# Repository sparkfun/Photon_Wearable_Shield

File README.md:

SparkFun Photon Wearable Shield

========================================

[*SparkFun Photon Wearable Shield (DEV-13328)*](https://www.sparkfun.com/products/13328)

The SparkFun Photon Wearable Shield makes it easy to add the WiFi enabled Photon to any wearables project. Each pin on the Photon is broken out into large sewing pins. Use conductive thread to make your next wearables projects. The large pins are also great for using conductive paint to create any project that needs WiFi. There are even optional smaller pins for soldering flexible wires. The SparkFun Photon Wearable Shield comes with the headers already soldered on, so you can plug and play!

The Particle Photon is a tiny WiFi development kit for creating connected projects and products. Sporting a 120Mhz ARM Cortex M3 and built-in WiFi, the Photon is not only powerful, but easy to use. The small form factor is ideal for IoT projects with cloud-connectivity.

Note: This Photon Wearable Shield does not include a Photon module and is currently available for preorder with a tentative release date of June 2015.

Features:

* 24 Large Sewing Tabs
* Headers and Connectors Pre-Soldered
* Compatible with the Photon and the Core

Repository Contents
-------------------

* **/Production** - Production panel files (.brd)
* **/Hardware** - Eagle design files (.brd, .sch)

Documentation
--------------
* **[SparkFun Photon Wearable Shield Hookup Guide](https://learn.sparkfun.com/tutorials/photon-wearable-shield-hookup-guide-)** - Basic hookup guide for the SparkFun Photon Wearable Shield.

License Information
-------------------

This product is _**open source**_! 

Please review the LICENSE.md file for license information. 

If you have any questions or concerns on licensing, please contact techsupport@sparkfun.com.

Distributed as-is; no warranty is given.

- Your friends at SparkFun.

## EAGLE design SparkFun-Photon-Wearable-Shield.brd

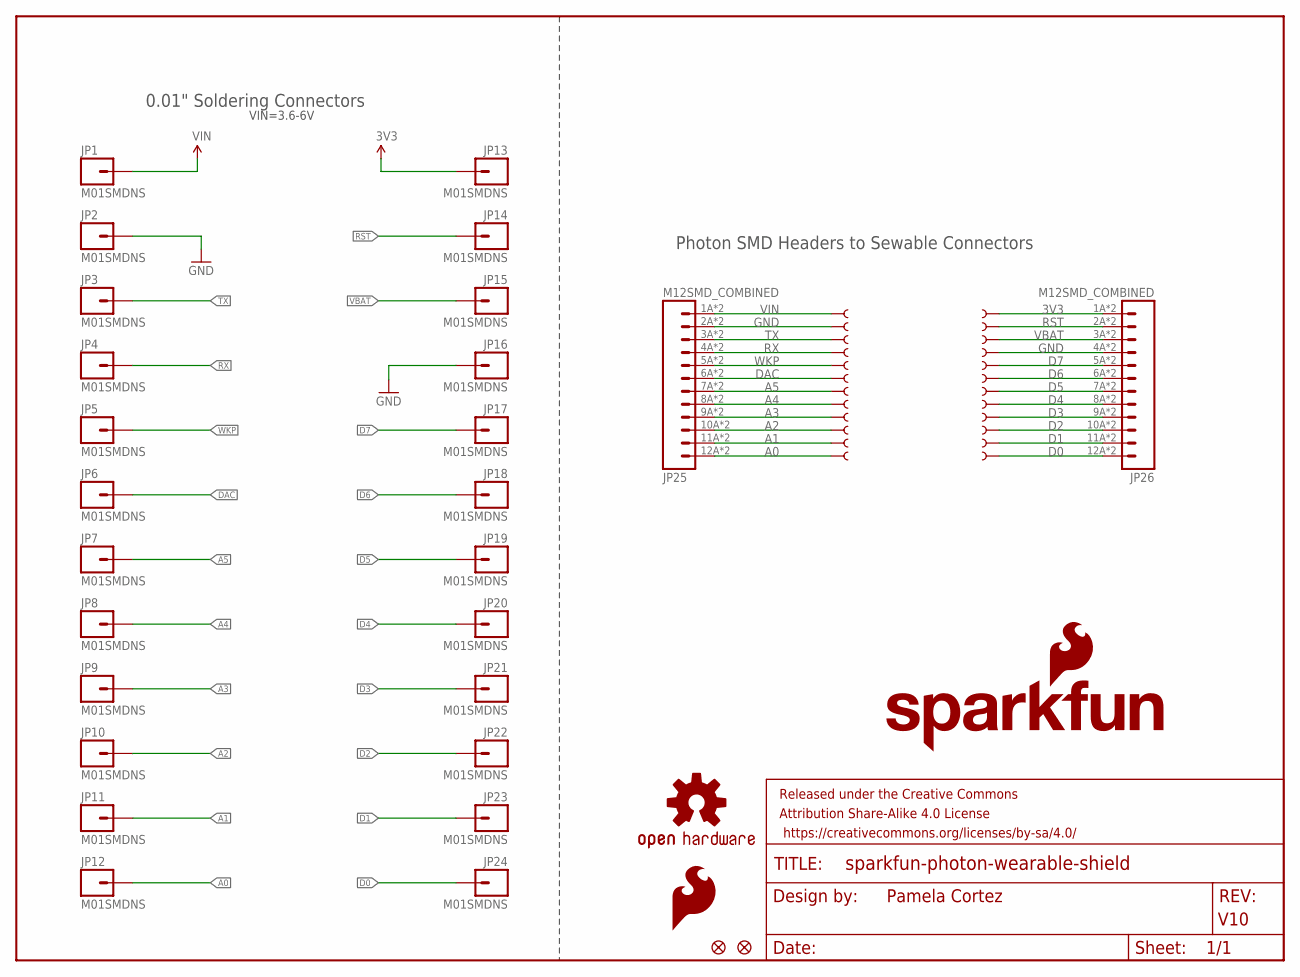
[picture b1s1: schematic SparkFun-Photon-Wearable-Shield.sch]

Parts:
FID1, FID2: FIDUCIAL1X2; FIDUCIAL-1X2
FRAME1: FRAME-LETTER; CREATIVE_COMMONS
J1, J2, J3, J4, J5, J6, J7, J8, J9, J10, J11, J12, J13, J14, J15, J16, J17, J18, J19, J20, J21, J22, J23, J24: PAD; PAD-LONG-2-SIDED
JP1, JP2, JP3, JP4, JP5, JP6, JP7, JP8, JP9, JP10, JP11, JP12, JP13, JP14, JP15, JP16, JP17, JP18, JP19, JP20, JP21, JP22, JP23, JP24: M01SMDNS; 1X01NS
JP25, JP26: M12SMD_COMBINED; 1X12_SMD_COMBINED
LOGO1: SFE_LOGO_FLAME.2_INCH; SFE_LOGO_FLAME_.2
LOGO2: OSHW-LOGOM; OSHW-LOGO-M
LOGO3: SFE_LOGO_NAME_FLAME.1_INCH; SFE_LOGO_NAME_FLAME_.1

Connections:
3V3: J13.1, JP13.1, JP26.1A (1), JP26.1B (1)
A0: J12.1, JP12.1, JP25.12A (12), JP25.12B (12)
A1: J11.1, JP11.1, JP25.11A (11), JP25.11B (11)
A2: J10.1, JP10.1, JP25.10A (10), JP25.10B (10)
A3: J9.1, JP9.1, JP25.9A (9), JP25.9B (9)
A4: J8.1, JP8.1, JP25.8A (8), JP25.8B (8)
A5: J7.1, JP7.1, JP25.7A (7), JP25.7B (7)
D0: J24.1, JP24.1, JP26.12A (12), JP26.12B (12)
D1: J23.1, JP23.1, JP26.11A (11), JP26.11B (11)
D2: J22.1, JP22.1, JP26.10A (10), JP26.10B (10)
D3: J21.1, JP21.1, JP26.9A (9), JP26.9B (9)
D4: J20.1, JP20.1, JP26.8A (8), JP26.8B (8)
D5: J19.1, JP19.1, JP26.7A (7), JP26.7B (7)
D6: J18.1, JP18.1, JP26.6A (6), JP26.6B (6)
D7: J17.1, JP17.1, JP26.5A (5), JP26.5B (5)
DAC: J6.1, JP6.1, JP25.6A (6), JP25.6B (6)
GND: J2.1, J16.1, JP2.1, JP16.1, JP25.2A (2), JP25.2B (2), JP26.4A (4), JP26.4B (4)
RST: J14.1, JP14.1, JP26.2A (2), JP26.2B (2)
RX: J4.1, JP4.1, JP25.4A (4), JP25.4B (4)
TX: J3.1, JP3.1, JP25.3A (3), JP25.3B (3)
VBAT: J15.1, JP15.1, JP26.3A (3), JP26.3B (3)
VIN: J1.1, JP1.1, JP25.1A (1), JP25.1B (1)
WKP: J5.1, JP5.1, JP25.5A (5), JP25.5B (5)

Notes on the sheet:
Pamela Cortez
V10
0.01" Soldering Connectors
Photon SMD Headers to Sewable Connectors
VIN=3.6-6V

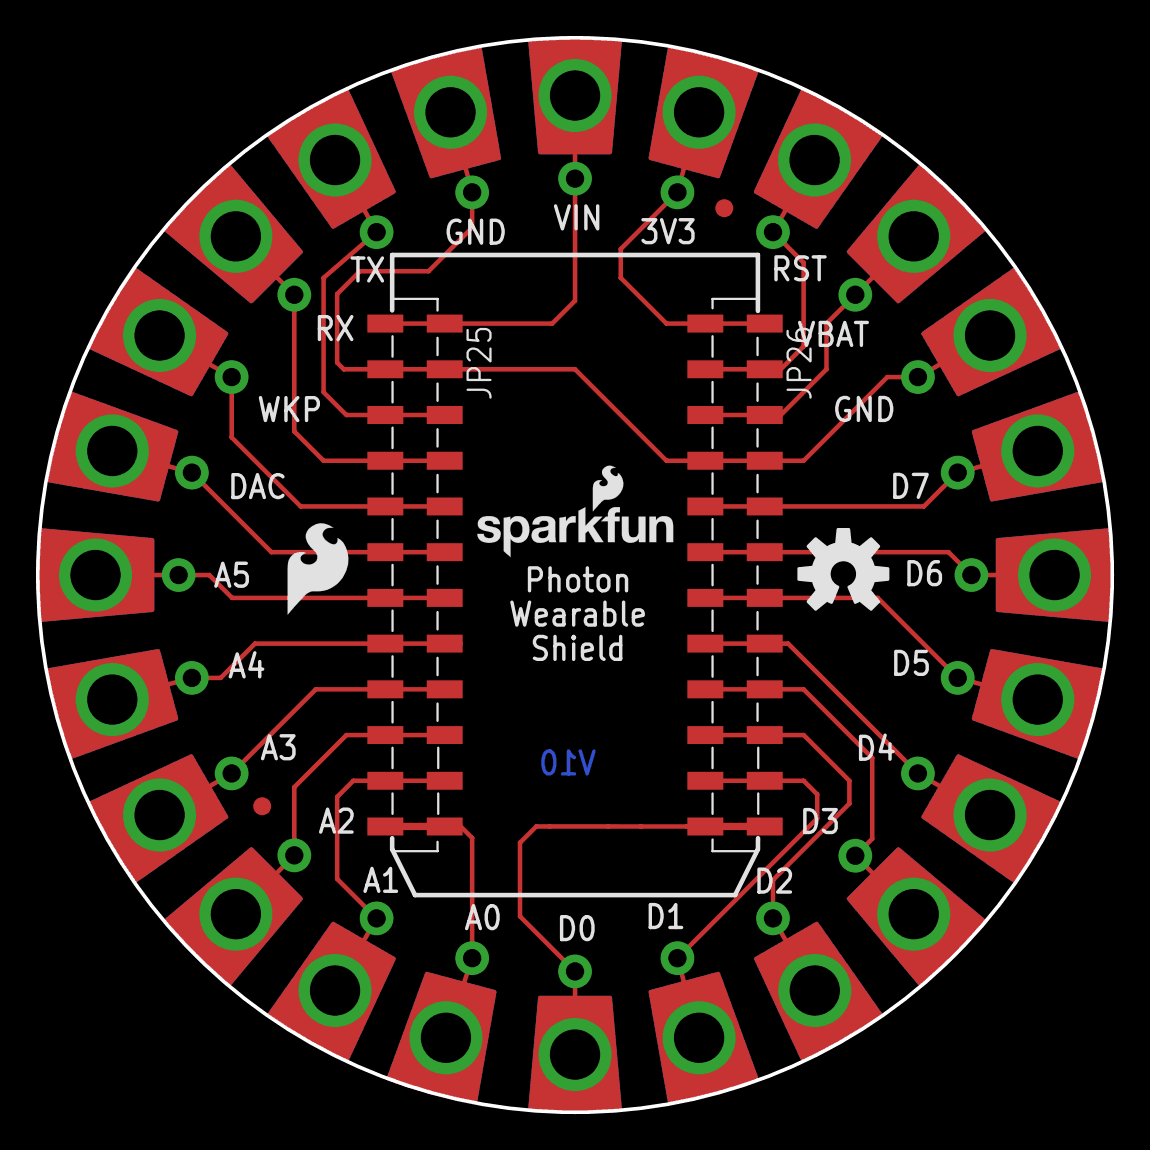
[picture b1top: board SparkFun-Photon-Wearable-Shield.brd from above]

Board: 2 copper layers, 59.7 x 59.7 mm, 57 parts (1 on the bottom side), 23 nets.

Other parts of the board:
U$2: SFE_LOGO_FLAME_.9

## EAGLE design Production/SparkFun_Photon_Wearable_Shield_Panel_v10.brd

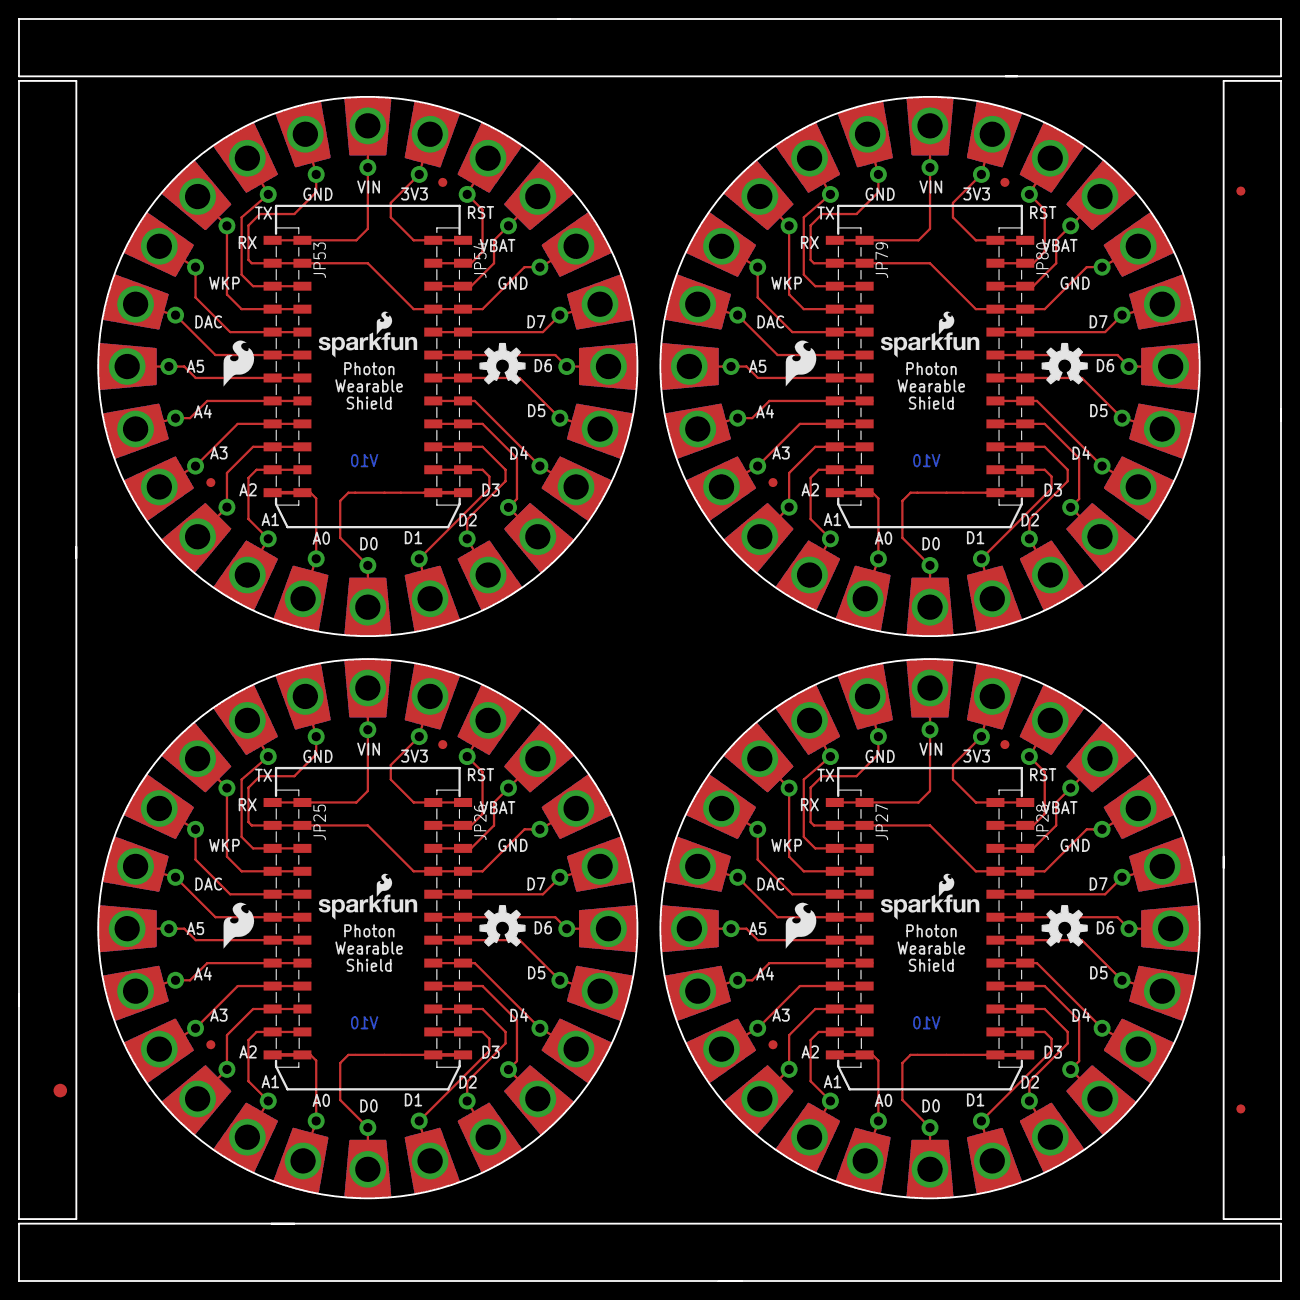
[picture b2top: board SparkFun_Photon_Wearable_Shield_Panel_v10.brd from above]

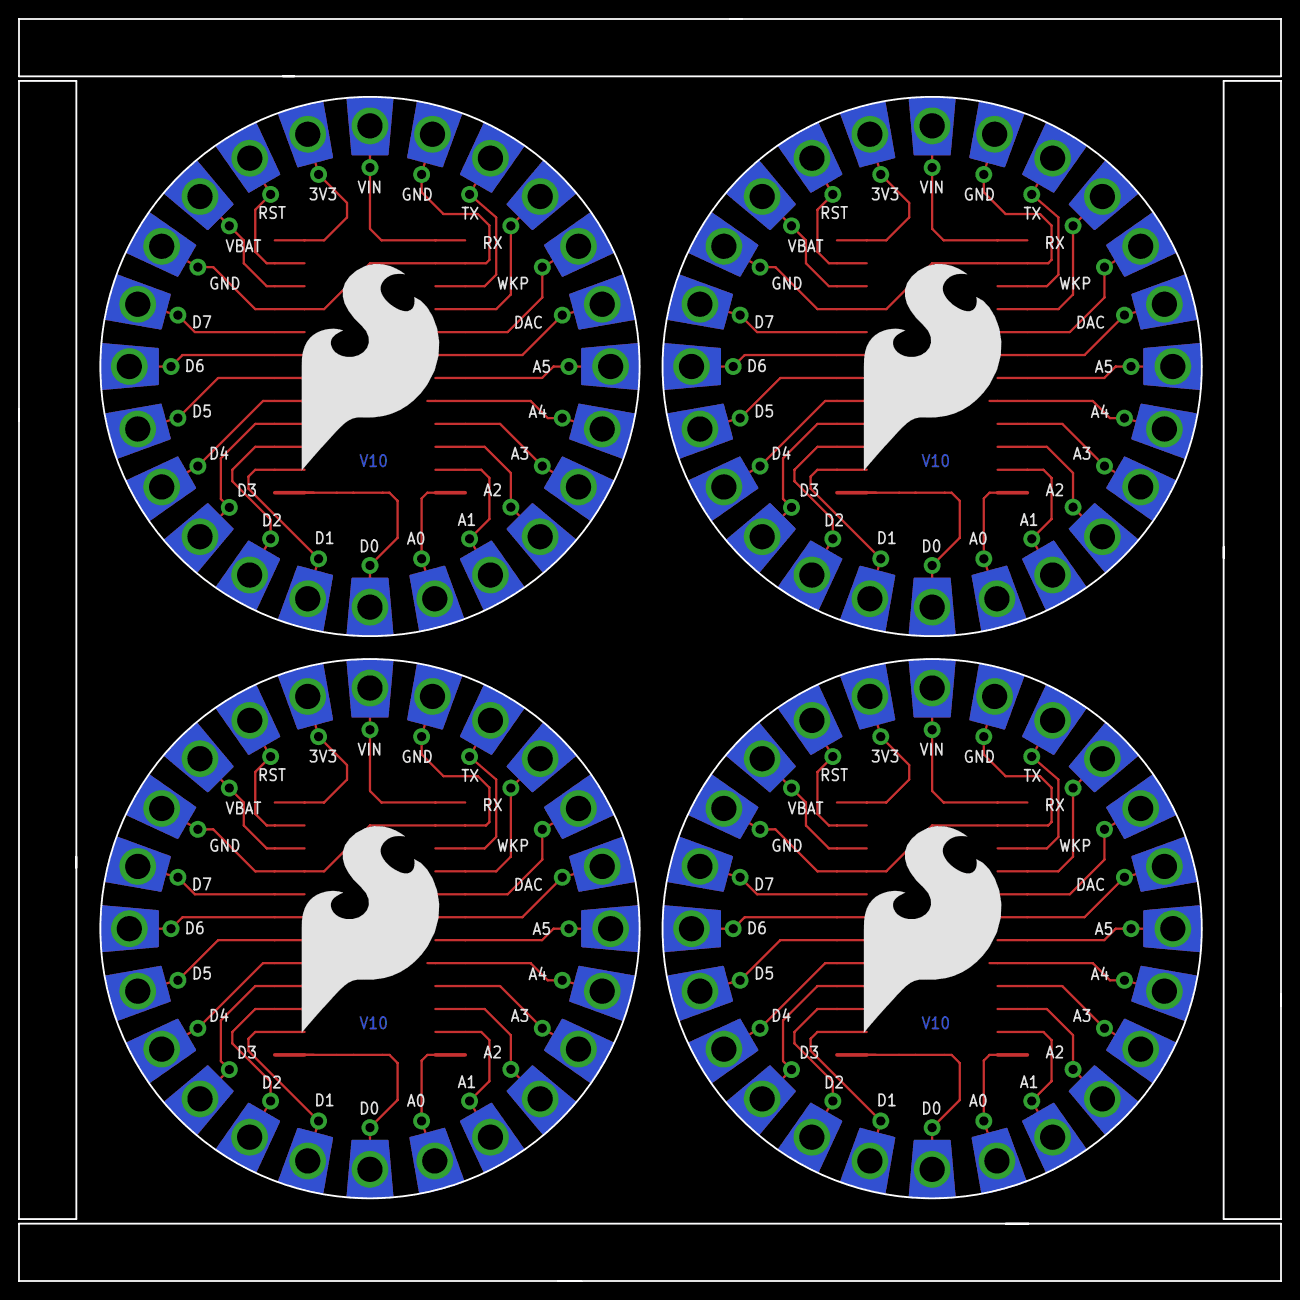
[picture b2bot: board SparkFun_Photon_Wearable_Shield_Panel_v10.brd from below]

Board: 2 copper layers, 139.7 x 139.7 mm, 227 parts (4 on the bottom side), 92 nets.

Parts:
E$1: FIDUCIAL-1.5X3
E$4, E$5: FIDUCIAL-1X2
FID1, FID2, FID3, FID4, FID5, FID6, FID7, FID8: FIDUCIAL1X2; FIDUCIAL-1X2
J1, J2, J3, J4, J5, J6, J7, J8, J9, J10, J11, J12, J13, J14, J15, J16, J17, J18, J19, J20, J21, J22, J23, J24, J25, J26, J27, J28, J29, J30, J31, J32, J33, J34, J35, J36, J37, J38, J39, J40, J41, J42, J43, J44, J45, J46, J47, J48, J49, J50, J51, J52, J53, J54, J55, J56, J57, J58, J59, J60, J61, J62, J63, J64, J65, J66, J67, J68, J69, J70, J71, J72, J73, J74, J75, J76, J77, J78, J79, J80, J81, J82, J83, J84, J85, J86, J87, J88, J89, J90, J91, J92, J93, J94, J95, J96: PAD; PAD-LONG-2-SIDED
JP1, JP2, JP3, JP4, JP5, JP6, JP7, JP8, JP9, JP10, JP11, JP12, JP13, JP14, JP15, JP16, JP17, JP18, JP19, JP20, JP21, JP22, JP23, JP24, JP29, JP30, JP31, JP32, JP33, JP34, JP35, JP36, JP37, JP38, JP39, JP40, JP41, JP42, JP43, JP44, JP45, JP46, JP47, JP48, JP49, JP50, JP51, JP52, JP55, JP56, JP57, JP58, JP59, JP60, JP61, JP62, JP63, JP64, JP65, JP66, JP67, JP68, JP69, JP70, JP71, JP72, JP73, JP74, JP75, JP76, JP77, JP78, JP81, JP82, JP83, JP84, JP85, JP86, JP87, JP88, JP89, JP90, JP91, JP92, JP93, JP94, JP95, JP96, JP97, JP98, JP99, JP100, JP101, JP102, JP103, JP104: M01SMDNS; 1X01NS
JP25, JP26, JP27, JP28, JP53, JP54, JP79, JP80: M12SMD_COMBINED; 1X12_SMD_COMBINED
LOGO1, LOGO4, LOGO7, LOGO10: SFE_LOGO_FLAME.2_INCH; SFE_LOGO_FLAME_.2
LOGO2, LOGO5, LOGO8, LOGO11: OSHW-LOGOM; OSHW-LOGO-M
LOGO3, LOGO6, LOGO9, LOGO12: SFE_LOGO_NAME_FLAME.1_INCH; SFE_LOGO_NAME_FLAME_.1
U$1, U$2, U$3, U$4: SFE_LOGO_FLAME_.9

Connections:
3V1: J48.1, JP28.1A, JP28.1B, JP52.1
3V2: J72.1, JP54.1A, JP54.1B, JP78.1
3V3: J13.1, JP13.1, JP26.1A, JP26.1B
3V4: J96.1, JP80.1A, JP80.1B, JP104.1
A0: J12.1, JP12.1, JP25.12A, JP25.12B
A1: J11.1, JP11.1, JP25.11A, JP25.11B
A2: J10.1, JP10.1, JP25.10A, JP25.10B
A3: J9.1, JP9.1, JP25.9A, JP25.9B
A4: J8.1, JP8.1, JP25.8A, JP25.8B
A5: J7.1, JP7.1, JP25.7A, JP25.7B
A6: J31.1, JP27.7A, JP27.7B, JP35.1
A7: J32.1, JP27.8A, JP27.8B, JP36.1
A8: J33.1, JP27.9A, JP27.9B, JP37.1
A9: J34.1, JP27.10A, JP27.10B, JP38.1
A10: J35.1, JP27.11A, JP27.11B, JP39.1
A11: J36.1, JP27.12A, JP27.12B, JP40.1
A12: J55.1, JP53.7A, JP53.7B, JP61.1
A13: J56.1, JP53.8A, JP53.8B, JP62.1
A14: J57.1, JP53.9A, JP53.9B, JP63.1
A15: J58.1, JP53.10A, JP53.10B, JP64.1
A16: J59.1, JP53.11A, JP53.11B, JP65.1
A17: J60.1, JP53.12A, JP53.12B, JP66.1
A18: J79.1, JP79.7A, JP79.7B, JP87.1
A19: J80.1, JP79.8A, JP79.8B, JP88.1
A20: J81.1, JP79.9A, JP79.9B, JP89.1
A21: J82.1, JP79.10A, JP79.10B, JP90.1
A22: J83.1, JP79.11A, JP79.11B, JP91.1
A23: J84.1, JP79.12A, JP79.12B, JP92.1
D0: J24.1, JP24.1, JP26.12A, JP26.12B
D1: J23.1, JP23.1, JP26.11A, JP26.11B
D2: J22.1, JP22.1, JP26.10A, JP26.10B
D3: J21.1, JP21.1, JP26.9A, JP26.9B
D4: J20.1, JP20.1, JP26.8A, JP26.8B
D5: J19.1, JP19.1, JP26.7A, JP26.7B
D6: J18.1, JP18.1, JP26.6A, JP26.6B
D7: J17.1, JP17.1, JP26.5A, JP26.5B
D8: J44.1, JP28.5A, JP28.5B, JP48.1
D9: J43.1, JP28.6A, JP28.6B, JP47.1
D10: J42.1, JP28.7A, JP28.7B, JP46.1
D11: J41.1, JP28.8A, JP28.8B, JP45.1
D12: J40.1, JP28.9A, JP28.9B, JP44.1
D13: J39.1, JP28.10A, JP28.10B, JP43.1
D14: J38.1, JP28.11A, JP28.11B, JP42.1
D15: J37.1, JP28.12A, JP28.12B, JP41.1
D16: J68.1, JP54.5A, JP54.5B, JP74.1
D17: J67.1, JP54.6A, JP54.6B, JP73.1
D18: J66.1, JP54.7A, JP54.7B, JP72.1
D19: J65.1, JP54.8A, JP54.8B, JP71.1
D20: J64.1, JP54.9A, JP54.9B, JP70.1
D21: J63.1, JP54.10A, JP54.10B, JP69.1
D22: J62.1, JP54.11A, JP54.11B, JP68.1
D23: J61.1, JP54.12A, JP54.12B, JP67.1
D24: J92.1, JP80.5A, JP80.5B, JP100.1
D25: J91.1, JP80.6A, JP80.6B, JP99.1
D26: J90.1, JP80.7A, JP80.7B, JP98.1
D27: J89.1, JP80.8A, JP80.8B, JP97.1
D28: J88.1, JP80.9A, JP80.9B, JP96.1
D29: J87.1, JP80.10A, JP80.10B, JP95.1
D30: J86.1, JP80.11A, JP80.11B, JP94.1
D31: J85.1, JP80.12A, JP80.12B, JP93.1
DAC: J6.1, JP6.1, JP25.6A, JP25.6B
DAC1: J30.1, JP27.6A, JP27.6B, JP34.1
DAC2: J54.1, JP53.6A, JP53.6B, JP60.1
DAC3: J78.1, JP79.6A, JP79.6B, JP86.1
GND: J2.1, J16.1, JP2.1, JP16.1, JP25.2A, JP25.2B, JP26.4A, JP26.4B
GND1: J26.1, J45.1, JP27.2A, JP27.2B, JP28.4A, JP28.4B, JP31.1, JP49.1
GND2: J50.1, J69.1, JP53.2A, JP53.2B, JP54.4A, JP54.4B, JP57.1, JP75.1
GND3: J74.1, J93.1, JP79.2A, JP79.2B, JP80.4A, JP80.4B, JP83.1, JP101.1
RST: J14.1, JP14.1, JP26.2A, JP26.2B
RST1: J47.1, JP28.2A, JP28.2B, JP51.1
RST2: J71.1, JP54.2A, JP54.2B, JP77.1
RST3: J95.1, JP80.2A, JP80.2B, JP103.1
RX: J4.1, JP4.1, JP25.4A, JP25.4B
RX1: J28.1, JP27.4A, JP27.4B, JP32.1
RX2: J52.1, JP53.4A, JP53.4B, JP58.1
RX3: J76.1, JP79.4A, JP79.4B, JP84.1
TX: J3.1, JP3.1, JP25.3A, JP25.3B
TX1: J27.1, JP27.3A, JP27.3B, JP30.1
TX2: J51.1, JP53.3A, JP53.3B, JP56.1
TX3: J75.1, JP79.3A, JP79.3B, JP82.1
VBAT: J15.1, JP15.1, JP26.3A, JP26.3B
VBAT1: J46.1, JP28.3A, JP28.3B, JP50.1
VBAT2: J70.1, JP54.3A, JP54.3B, JP76.1
VBAT3: J94.1, JP80.3A, JP80.3B, JP102.1
VIN: J1.1, JP1.1, JP25.1A, JP25.1B
VIN1: J25.1, JP27.1A, JP27.1B, JP29.1
VIN2: J49.1, JP53.1A, JP53.1B, JP55.1
VIN3: J73.1, JP79.1A, JP79.1B, JP81.1
WKP: J5.1, JP5.1, JP25.5A, JP25.5B
WKP1: J29.1, JP27.5A, JP27.5B, JP33.1
WKP2: J53.1, JP53.5A, JP53.5B, JP59.1
WKP3: J77.1, JP79.5A, JP79.5B, JP85.1

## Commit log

2015-03-31 Eagle Board and Schematic
    Initial commit
2015-04-01 Updating Boards
2015-05-21 Updating board files
    V10
2015-05-28 created panel v10
2015-07-02 Adding Hardware and README.md
2015-07-02 Adding README.md

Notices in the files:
parts and their libraries:
SparkFun-Aesthetics: Licensing: Creative Commons ShareAlike 4.0 International - https://creativecommons.org/licenses/by-sa/4.0
SparkFun-Aesthetics: Released under the Creative Commons Attribution Share-Alike 4.0 License
SparkFun-Aesthetics: https://creativecommons.org/licenses/by-sa/4.0
